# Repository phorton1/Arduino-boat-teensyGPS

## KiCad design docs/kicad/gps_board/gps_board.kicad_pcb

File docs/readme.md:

# teensyGPS

**Home**

repos: **[phorton1](https://github.com/phorton1)** --
**[teensyBoat Firmware](https://github.com/phorton1/Arduino-boat-teensyBoat/blob/master/docs/readme.md)** --
**[teensyBoat App](https://github.com/phorton1/base-apps-teensyBoat/blob/master/docs/readme.md)** --
**[Boat Library](https://github.com/phorton1/Arduino-libraries-Boat/blob/master/docs/readme.md)** --
**[tbESP32 WiFi](https://github.com/phorton1/Arduino-boat-tbESP32/blob/master/docs/readme.md)** --
**[teensyWind Tester](https://github.com/phorton1/Arduino-boat-teensyWind/blob/master/docs/readme.md)** --
**teensyGPS**

**teensyGPS** is a Teensy 4.0 firmware and custom PCB that turns a u-blox
**Neo-6M** GPS module into a drop-in GPS source for Raymarine marine instrument
networks.  It reads the standard NMEA 0183 sentence stream from the Neo-6M,
builds a complete GPS model (position, COG, SOG, fix quality, satellite data,
date and time), syncs the Teensy's real-time clock from the GPS fix, and
re-broadcasts everything as **Seatalk1** datagrams and/or **NMEA 2000** packets
every second.

The device is built on the shared
**[Arduino Boat Library](https://github.com/phorton1/Arduino-libraries-Boat/blob/master/docs/readme.md)**,
which provides the Seatalk1 encoding helpers and the NMEA 2000 object.  It
lives in a 3D-printed enclosure mounted on a custom home-milled PCB.

TODO: insert photo of teensyGPS device here

## Protocol Output

### Seatalk1

When Seatalk1 output is enabled, teensyGPS transmits a complete set of GPS
datagrams every second:

- **Position** (ST_LATLON, 0x58) -- latitude and longitude
- **COG** (0x53) -- course over ground, converted to magnetic using the
  Boat library's magnetic declination model
- **SOG** (0x52) -- speed over ground in knots
- **Date** (0x56) and **Time** (0x54) -- UTC date and time from GPS fix
- **Satellite summary** (ST_SAT_INFO, 0x57) -- fix type and HDOP
- **Satellite detail** (ST_SAT_DETAIL, 0xA5) -- fix quality, HDOP fields
- **Per-satellite data** -- PRN, elevation, azimuth, SNR, and used-in-solution
  flag, up to the Seatalk maximum, in PRN order

The device also **receives** and responds to Seatalk1:

- **Device queries** (0xA4) -- identifies itself as a Raymarine RS125 GPS
  (Seatalk unit ID 0xC5)
- **Restart GPS button** on the Raymarine E80 -- a specific 0xA5/0x4D
  datagram pattern causes the firmware to send the expected reply and then
  reboot, making the E80's Restart GPS button work correctly

### NMEA 2000

When NMEA 2000 output is enabled, teensyGPS transmits four PGNs per second:

| PGN    | Name                    | Content                                      |
| ------ | ----------------------- | -------------------------------------------- |
| 129029 | GNSS Position Data      | lat, lon, altitude, fix type, sats, DOP      |
| 130577 | Direction Data          | COG (true) and SOG                           |
| 126992 | System Date/Time        | UTC time from GPS, GPS source                |
| 129540 | GNSS Satellites in View | per-satellite PRN, elev, azimuth, SNR, usage |

The device registers with NMEA 2000 as a **Positioning System** (function 130,
class 60) named "teensyGPS_device".

## Serial Console and Configuration

teensyGPS has a persistent **serial console UI** accessible via any USB serial
terminal at 921600 baud.  Settings are stored in EEPROM (base offset 256,
separate from the teensyBoat range at 512) and survive power cycles.

Type `?` for help.  Commands use the `NAME=VALUE` or bare-word format:

| Command        | Description                                          |
| -------------- | ---------------------------------------------------- |
| `SEATALK=0/1`  | Enable or disable Seatalk1 output (default: enabled) |
| `NMEA2000=0/1` | Enable or disable NMEA 2000 output (default: off)    |
| `SAVE`         | Save current settings to EEPROM                      |
| `LOAD`         | Load settings from EEPROM                            |
| `reboot`       | Software-reboot the Teensy                           |
| `L`            | List all NMEA 2000 devices on the bus (with product info) |
| `Q`            | Send a device query to all NMEA 2000 devices         |
| `M_ST=N`       | Monitor incoming Seatalk1 datagrams (0=off, 1=on)    |
| `M_2000=N`     | Monitor NMEA 2000 traffic (bitmask, see below)       |

### Protocol Monitoring

The monitoring commands tap into the Boat library's full **named-datagram
decoders**.  With `M_ST=1`, every incoming Seatalk1 datagram is decoded and
printed by name -- DEPTH, WIND_ANGLE, WIND_SPEED, WATER_SPEED, SOG, COG,
LATLON, SAT_INFO, AUTOPILOT, and others -- making teensyGPS a useful
live Seatalk1 bus monitor as well as a GPS source.

With `M_2000`, NMEA 2000 traffic is decoded and printed with PGN name,
priority, source address, and data, with separate bitmask control over
which traffic categories are shown:

| Bit    | Meaning                                      |
| ------ | -------------------------------------------- |
| 0x0001 | Sensor output and known incoming messages    |
| 0x0002 | GPS and AIS messages specifically            |
| 0x0004 | Known proprietary incoming messages          |
| 0x0008 | Unknown (non-bus, non-proprietary) incoming  |
| 0x0010 | Bus traffic in                               |
| 0x0020 | Bus traffic out                              |
| 0x1000 | Include self-sent messages in monitoring     |
| 0x8000 | Show raw instrument messages                 |

The `L` and `Q` commands use the Boat library's NMEA 2000 device list to
enumerate all devices on the bus and display their manufacturer name,
model ID, software version, and NMEA 2000 source address -- useful for
understanding what else is on the network.

## Genuine vs. Clone Neo-6M

At startup teensyGPS sends a UBX-MON-VER query to the GPS module and checks the
response for the string "SW VERSION:" -- a signature present in genuine u-blox
modules but absent in common clone modules.  Genuine modules do not need to be
configured to suppress GLONASS and BeiDou sentences; clones cannot be configured
to suppress them.  Either type works: teensyGPS filters the constellation
explicitly, processing only `$GPGSV` sentences (GPS satellites) and ignoring
`$BDGSV` (BeiDou) to maintain E80 chartplotter compatibility.

## Boat Library Dependency

teensyGPS uses the
**[Arduino Boat Library](https://github.com/phorton1/Arduino-libraries-Boat/blob/master/docs/readme.md)**
for three things:

- **`instST.h`** -- Seatalk1 datagram queue, send, and satellite-data helper
  functions (`queueDatagram`, `sendDatagram`, `initStSatMessages`,
  `addStSatMessage`, `queueStSatMessages`, `clearSTQueues`, and the
  `ST_*` datagram constants)
- **`inst2000.h`** -- the NMEA 2000 bus object and PGN send helpers
- **`boatSimulator.h`** -- `boat_sim.makeMagnetic()` to convert true COG
  to magnetic before encoding the Seatalk1 COG datagram

## Files Available

Hardware design files are included in this repository:

- **docs/kicad/gps_board/** -- KiCad schematic and PCB layout for the GPS board.
  TODO: insert schematic image here
  TODO: insert PCB layout image here
- **docs/kicad/gps_board/plot/** -- Gerber files for fabrication.
- **docs/kicad/gps_board/plot/gcode/** -- CNC milling gcode for the home-milled
  PCB: isolate, laser mark, drill, mill holes, cutout.
- **docs/3dp/** -- 3D-printed enclosure parts:
  - **gps_case.stl** -- main enclosure body
  - **gps_top.stl** -- top cover
  - **gps_mount.stl** -- mounting bracket (printed in ASA for UV resistance)
  - **neo_support.stl** -- internal support bracket for the Neo-6M module
  - **gps_test_nut1.stl** and **gps_test_nut2.stl** -- connector test fixtures
  - **gps_box.f3d** -- Fusion 360 source file for the enclosure

## Credits

- [**Paul Stoffregen**](https://www.pjrc.com/teensy/) --
  Creator of the Teensy microcontroller platform.  teensyGPS is built
  for the Teensy 4.0.

- [**Thomas Knauf**](http://www.thomasknauf.de/seatalk.htm) --
  *SeaTalk Technical Reference Revision 3.23*.  The primary public reference for
  the Seatalk1 datagram protocol.  The
  **[Arduino Boat Library](https://github.com/phorton1/Arduino-libraries-Boat/blob/master/docs/readme.md)**
  used by this firmware builds on, extends, and in places corrects that work.

## License

This software is released under the
[**GNU General Public License v3**](../LICENSE.TXT).

## Please Also See

- [**phorton1/Arduino-libraries-Boat**](https://github.com/phorton1/Arduino-libraries-Boat) --
  The shared Arduino C++ library used by this firmware.  Provides Seatalk1 and
  NMEA 2000 protocol encoding, satellite data helpers, and the magnetic
  declination model.

- [**phorton1/Arduino-boat-teensyBoat**](https://github.com/phorton1/Arduino-boat-teensyBoat) --
  The related multi-protocol marine instrument bridge using the same Boat library.
  Bridges Seatalk1, NMEA 0183, and NMEA 2000; includes a virtual boat simulator
  and a desktop test harness for Raymarine ST50 instruments.

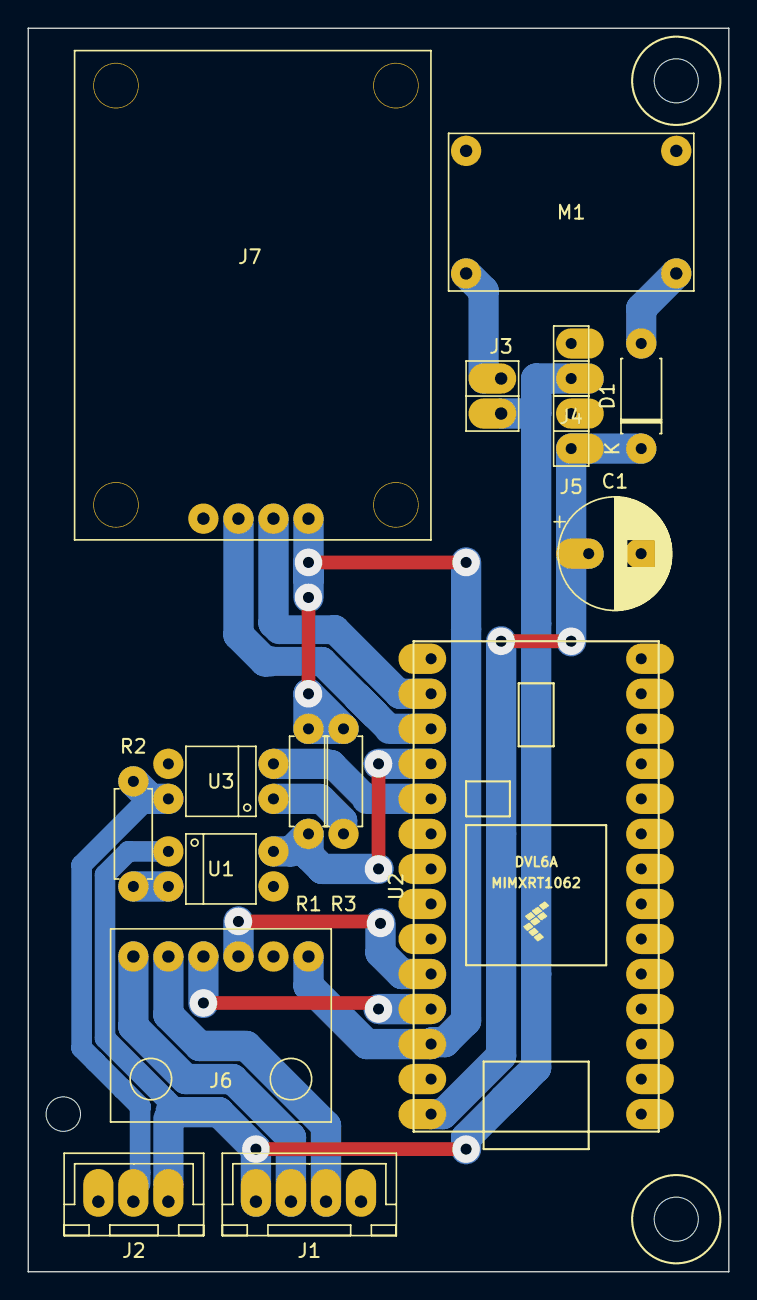
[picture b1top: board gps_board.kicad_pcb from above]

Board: 2 copper layers, 50.8 x 90.2 mm, 16 parts (0 on the bottom side), 17 nets.

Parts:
C1: 100uf; CP_my100uf
D1: 1N5819; myDiodeSchotsky
J1: NMEA2000; JST4
J2: SEATALK; JST3
J3: BUCK_PWR; pinHeader1x2
J4: 12V_TEST; pinSocket1x2
J5: 5V_TEST; pinSocket1x2
J6: SN65HVD230; CANBUS_Module1
J7: NEO6M; neo6m
M1: BUCK01; myMini360BuckConverter
R1: 10K; myResistor
R2: 4.7K; myResistor
R3: 220; myResistor
U1, U3: TLP521; myDip4
U2: myTeensy4.0; teensy40

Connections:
+3V3: J6.1, J7.4, R1.1, R3.2, U2.26
+5V: C1.1, D1.1, J5.1, U2.28
+12V: J1.4, J2.1, J3.2, J4.1, U1.1
CANH: J1.2, J6.5
CANL: J1.3, J6.6
CRX: J6.3, U2.24
CTX: J6.4, U2.25
GND: C1.2, J1.1, J2.3, J4.2, J5.2, J6.2, J7.1, M1.1, M1.2, U1.3, U2.1, U2.27, U3.3
unnamed: D1.2, M1.3
unnamed: J3.1, M1.4
unnamed: R2.1, U1.2
unnamed: R3.1, U3.1
RX3: J7.2, U2.17
RX4: R1.2, U1.4, U2.18
ST1: J2.2, R2.2, U3.4
TX3: J7.3, U2.16
TX4: U2.19, U3.2

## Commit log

2026-02-04 different DEV_QUERIY sub_versions for ST GPS devices; implemented response to Restart GPS button implementeed newly found ST_TARGET_NAME/ST_TARGET_ID parsing
2026-02-06 Sanity checkin before rework for "real" teensyGPS.ino breadboard & possible PCB
2026-02-06 remove UI/implementation and move neoGPS to teensyGPS repo - cleanup NMEA2000 device (teensyBoat vs teensyGPS) initialization - update preferences.txt's to back two plugs on Lenovo3
2026-02-07 Be an NMEA2000 device even when not explicitly sending GPS PGN's
2026-02-12 fixed help typo
2026-02-20 new teensyGPS pcb gps_board
2026-02-20 rework teensyGPS incluging new pins, refactoring it and teensyBoat ST stuff, NMEA2000 init, and monitoring commands
2026-02-20 parse NMEA2000 PGN_SYSTEM_DATE_TIME; minor improvement to teeensyGPS help
2026-02-20 made seatalk and nmea2000 enabled into functions (i.e. runtime switches) only used for Output/Parsing; made E80 RestartGPS button reboot teensyGPS
2026-02-23 redesigned teensyGPS board (removed jumpers; needs EEPROM) before rotating for flatcam
2026-02-24 did flatcam stuff and milled teensyGPS PCB
2026-02-24 re-added EEPROM SEATALK=0/1/2 NMEA2000=0/1/2
2026-02-25 3d print case
2026-02-25 show resistor values switch jst jumpers
2026-02-25 go back to simple SEATALK/NMEA2000 0=off; 1=enabled to ensure init always happens
2026-04-03 add gcode .gitignores to project docs 3dp folders
2026-04-03 print teensyGPS antenna pod (gps mount)
2026-05-10 teensyBoat documentation pass

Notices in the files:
docs/readme.md:
License:
This software is released under the
[**GNU General Public License v3**](../LICENSE.TXT).
